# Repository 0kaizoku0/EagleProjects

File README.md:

# EagleProjects
This is the repo of my designed pcbs.

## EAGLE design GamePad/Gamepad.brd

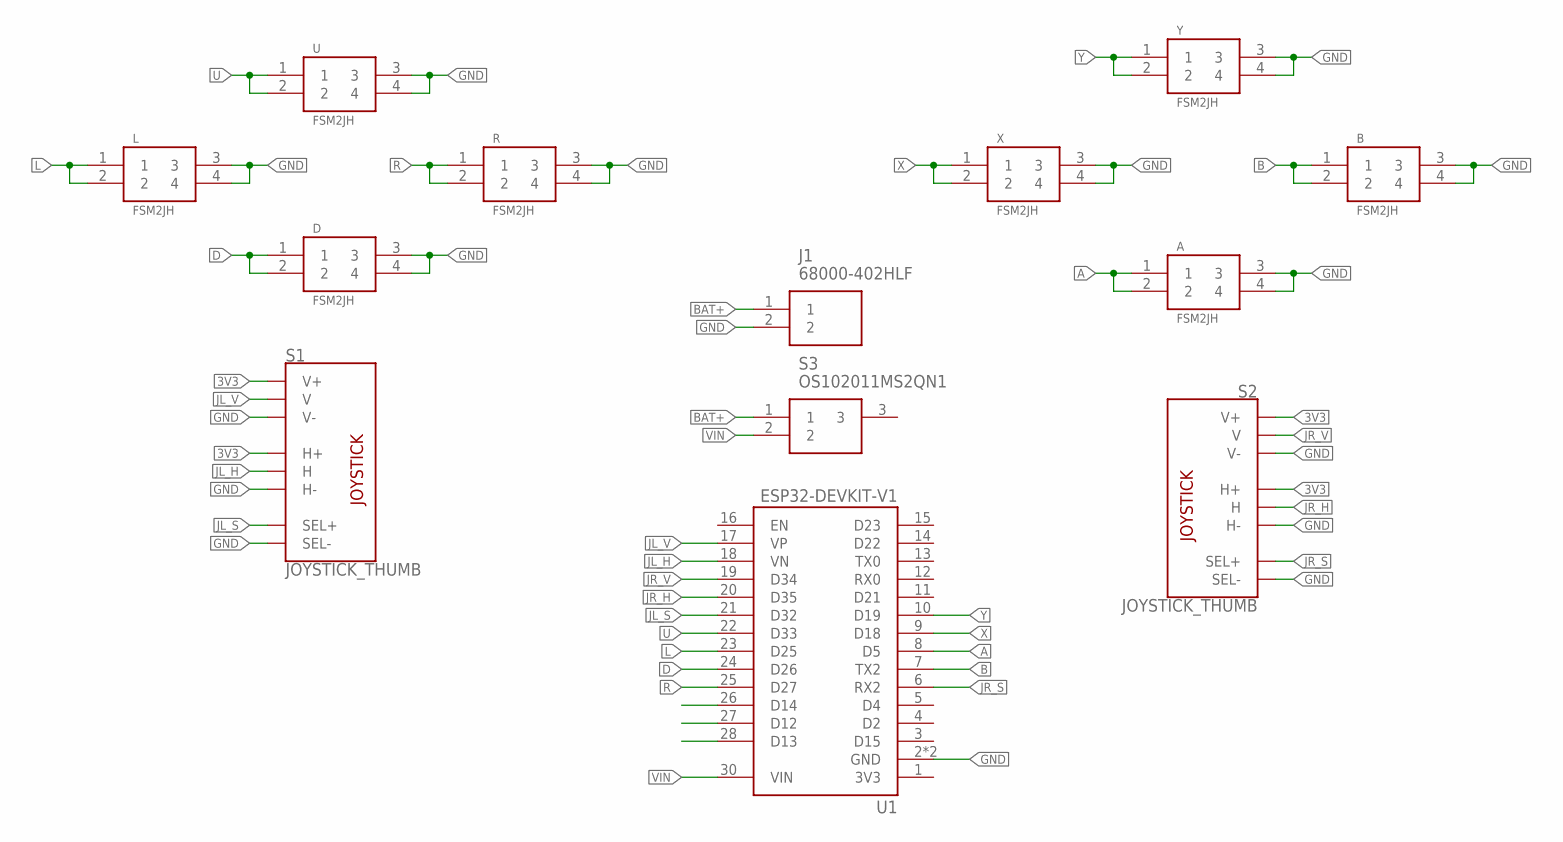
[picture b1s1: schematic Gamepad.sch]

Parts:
A: FSM2JH
B: FSM2JH
D: FSM2JH
J1: 68000-402HLF
L: FSM2JH
R: FSM2JH
S1, S2: JOYSTICK_THUMB; JOYSTICK
S3: OS102011MS2QN1; OS102011MA1QN1
U: FSM2JH
U1: ESP32-DEVKIT-V1; MODULE_ESP32_DEVKIT_V1
X: FSM2JH
Y: FSM2JH

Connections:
3V3: S1.H1 (H+), S1.V1 (V+), S2.H1 (H+), S2.V1 (V+)
A: A.1, A.2, U1.8 (D5)
B: B.1, B.2, U1.7 (TX2)
BAT+: J1.1, S3.1
D: D.1, D.2, U1.24 (D26)
GND: A.3, A.4, B.3, B.4, D.3, D.4, J1.2, L.3, L.4, R.3, R.4, S1.B2A (SEL-), S1.H3 (H-), S1.V3 (V-), S2.B2A (SEL-), S2.H3 (H-), S2.V3 (V-), U.3, U.4, U1.2 (GND), U1.29 (GND), X.3, X.4, Y.3, Y.4
JL_H: S1.H2 (H), U1.18 (VN)
JL_S: S1.B1A (SEL+), U1.21 (D32)
JL_V: S1.V2 (V), U1.17 (VP)
JR_H: S2.H2 (H), U1.20 (D35)
JR_S: S2.B1A (SEL+), U1.6 (RX2)
JR_V: S2.V2 (V), U1.19 (D34)
L: L.1, L.2, U1.23 (D25)
R: R.1, R.2, U1.25 (D27)
U: U.1, U.2, U1.22 (D33)
VIN: S3.2, U1.30 (VIN)
X: U1.9 (D18), X.1, X.2
Y: U1.10 (D19), Y.1, Y.2

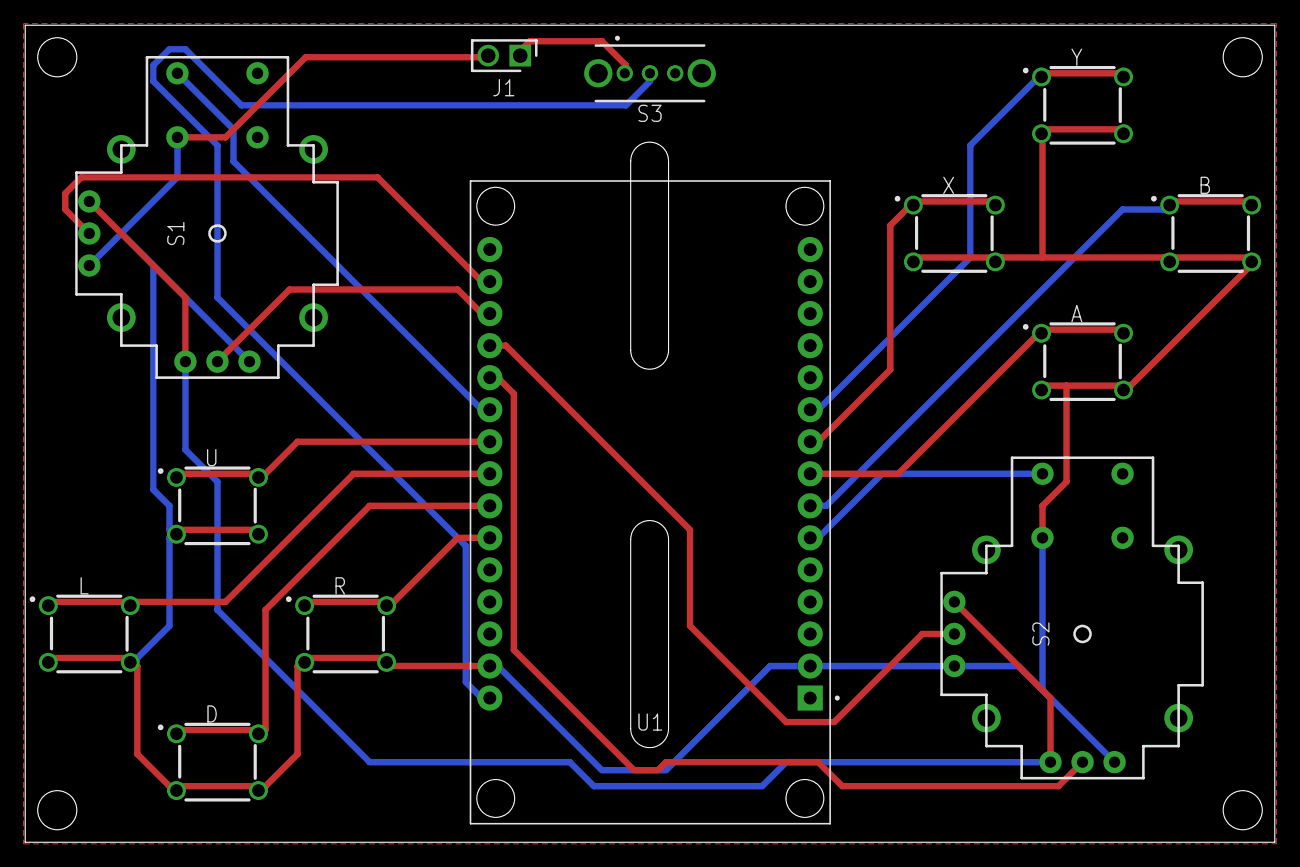
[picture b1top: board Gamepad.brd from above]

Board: 2 copper layers, 99.1 x 64.8 mm, 13 parts (0 on the bottom side), 18 nets.

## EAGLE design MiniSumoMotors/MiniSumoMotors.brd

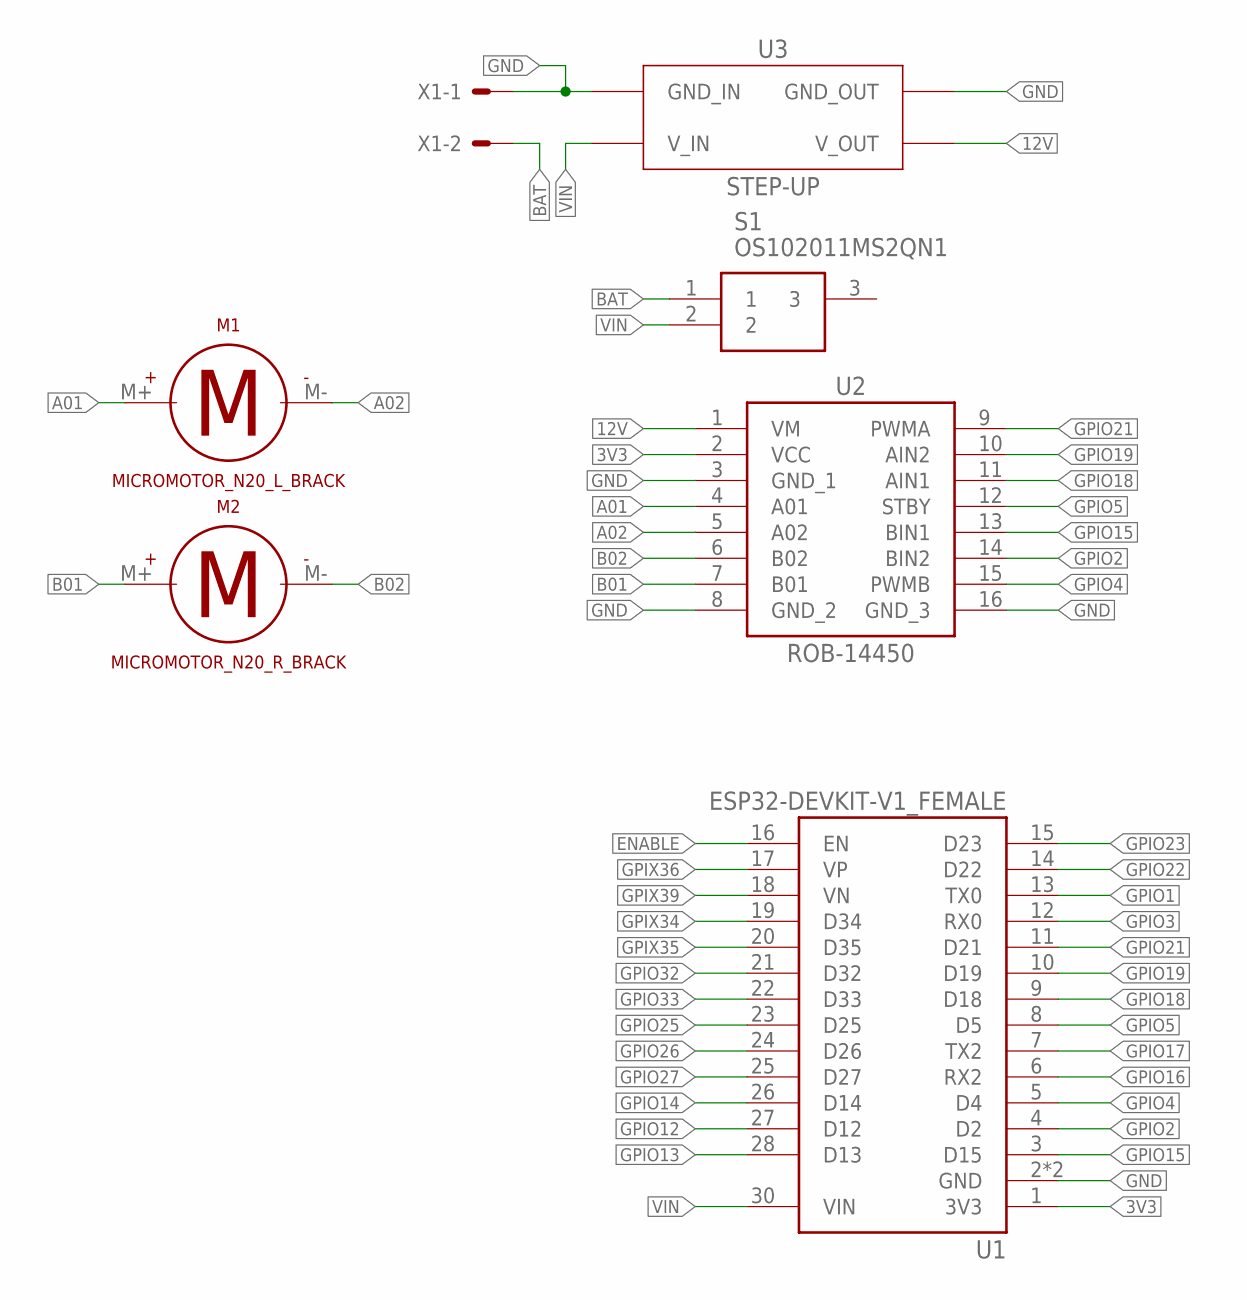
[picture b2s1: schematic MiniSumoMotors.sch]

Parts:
M1: MICROMOTOR_N20_L_BRACK; MICROMOTOR-L_BRACK
M2: MICROMOTOR_N20_R_BRACK; MICROMOTOR-R_BRACK
S1: OS102011MS2QN1; OS102011MA1QN1
U1: ESP32-DEVKIT-V1_FEMALE; MODULE_ESP32_DEVKIT_V1_FEMALE
U2: ROB-14450; ROB14450
U3: STEP-UP
X1: 22-23-2021

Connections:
3V3: U1.1 (3V3), U2.2 (VCC)
12V: U2.1 (VM), U3.V_OUT
A01: M1.M+, U2.4 (A01)
A02: M1.M-, U2.5 (A02)
B01: M2.M+, U2.7 (B01)
B02: M2.M-, U2.6 (B02)
BAT: S1.1, X1.2
ENABLE: U1.16 (EN)
GND: U1.2 (GND), U1.29 (GND), U2.3 (GND_1), U2.8 (GND_2), U2.16 (GND_3), U3.GND_IN, U3.GND_OUT, X1.1
GPIO1: U1.13 (TX0)
GPIO2: U1.4 (D2), U2.14 (BIN2)
GPIO3: U1.12 (RX0)
GPIO4: U1.5 (D4), U2.15 (PWMB)
GPIO5: U1.8 (D5), U2.12 (STBY)
GPIO12: U1.27 (D12)
GPIO13: U1.28 (D13)
GPIO14: U1.26 (D14)
GPIO15: U1.3 (D15), U2.13 (BIN1)
GPIO16: U1.6 (RX2)
GPIO17: U1.7 (TX2)
GPIO18: U1.9 (D18), U2.11 (AIN1)
GPIO19: U1.10 (D19), U2.10 (AIN2)
GPIO21: U1.11 (D21), U2.9 (PWMA)
GPIO22: U1.14 (D22)
GPIO23: U1.15 (D23)
GPIO25: U1.23 (D25)
GPIO26: U1.24 (D26)
GPIO27: U1.25 (D27)
GPIO32: U1.21 (D32)
GPIO33: U1.22 (D33)
GPIX34: U1.19 (D34)
GPIX35: U1.20 (D35)
GPIX36: U1.17 (VP)
GPIX39: U1.18 (VN)
VIN: S1.2, U1.30 (VIN), U3.V_IN

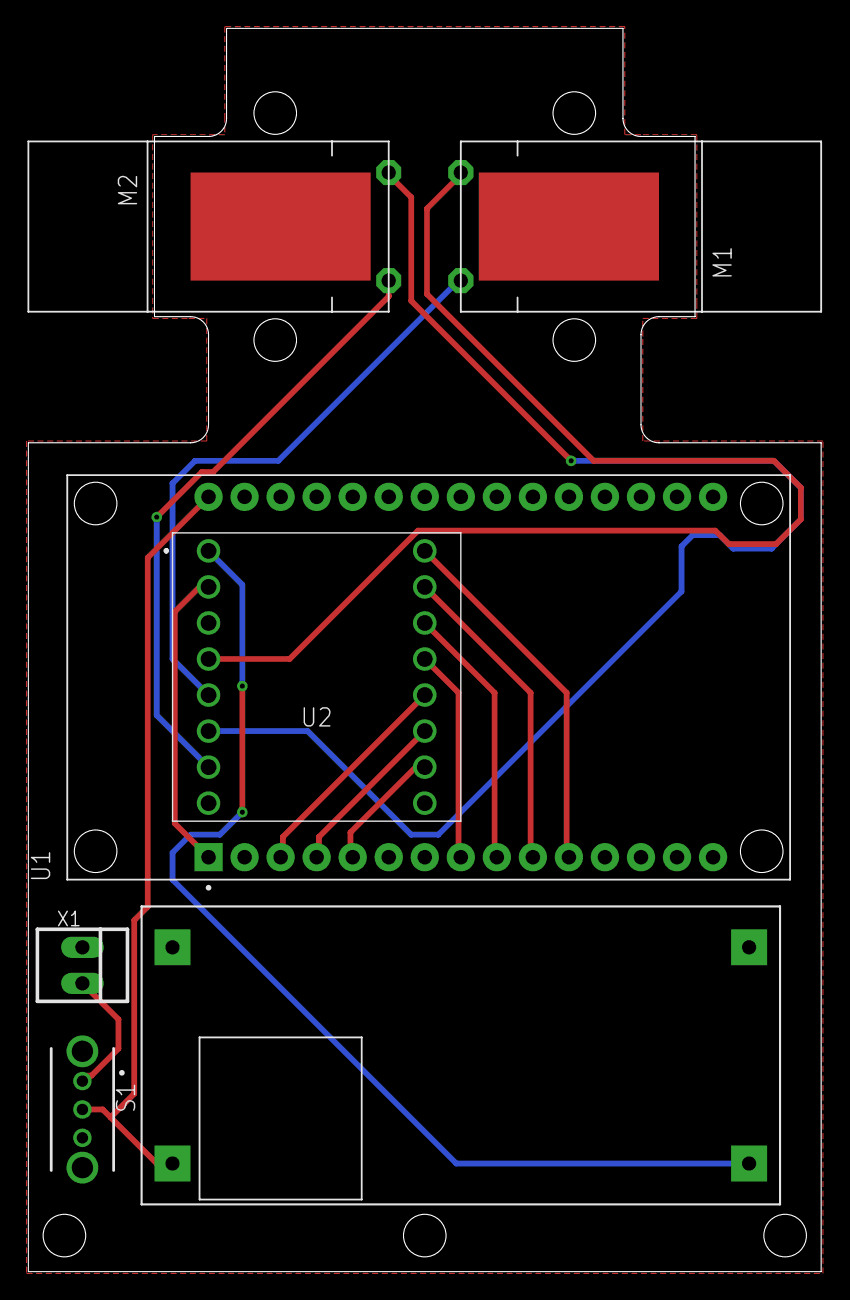
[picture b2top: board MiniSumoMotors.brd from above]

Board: 2 copper layers, 55.9 x 87.6 mm, 7 parts (0 on the bottom side), 16 nets.

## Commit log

2023-05-01 Starting repo with mini sumo RC
